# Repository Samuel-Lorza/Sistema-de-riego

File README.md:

# Sistema-de-riego automatico
Sistema de riego automatico con el uso del ESP32

## Integrantes:

Samuel Lorza-Miguel Pardo-Juan Crespo- Diego García

## Descripción

El presente proyecto, es un sistema de riego automático realizado con un microprocesador de referencia ESP32, la utilidad del sistema radica en la asistencia al usuario para regar plantas en momentos de ausencia, tales como un viaje, una reunión, o que el dueño este ocupado y no pueda cuidar de sus plantas. Con base en lo anterior, el sistema es totalmente programable en cuanto a la temperatura y la humedad que el usuario necesite, dependiendo de las necesidades de la planta. Se ha de mencionar que el usuario debe proveer de agua al sistema, por ejemplo, poniendo un tanque plástico con agua, además, el sistema hará un ruido con el objetivo de recordar al usuario de llenar el tanque (fuente de agua) cuando este tiene un bajo nivel de agua.

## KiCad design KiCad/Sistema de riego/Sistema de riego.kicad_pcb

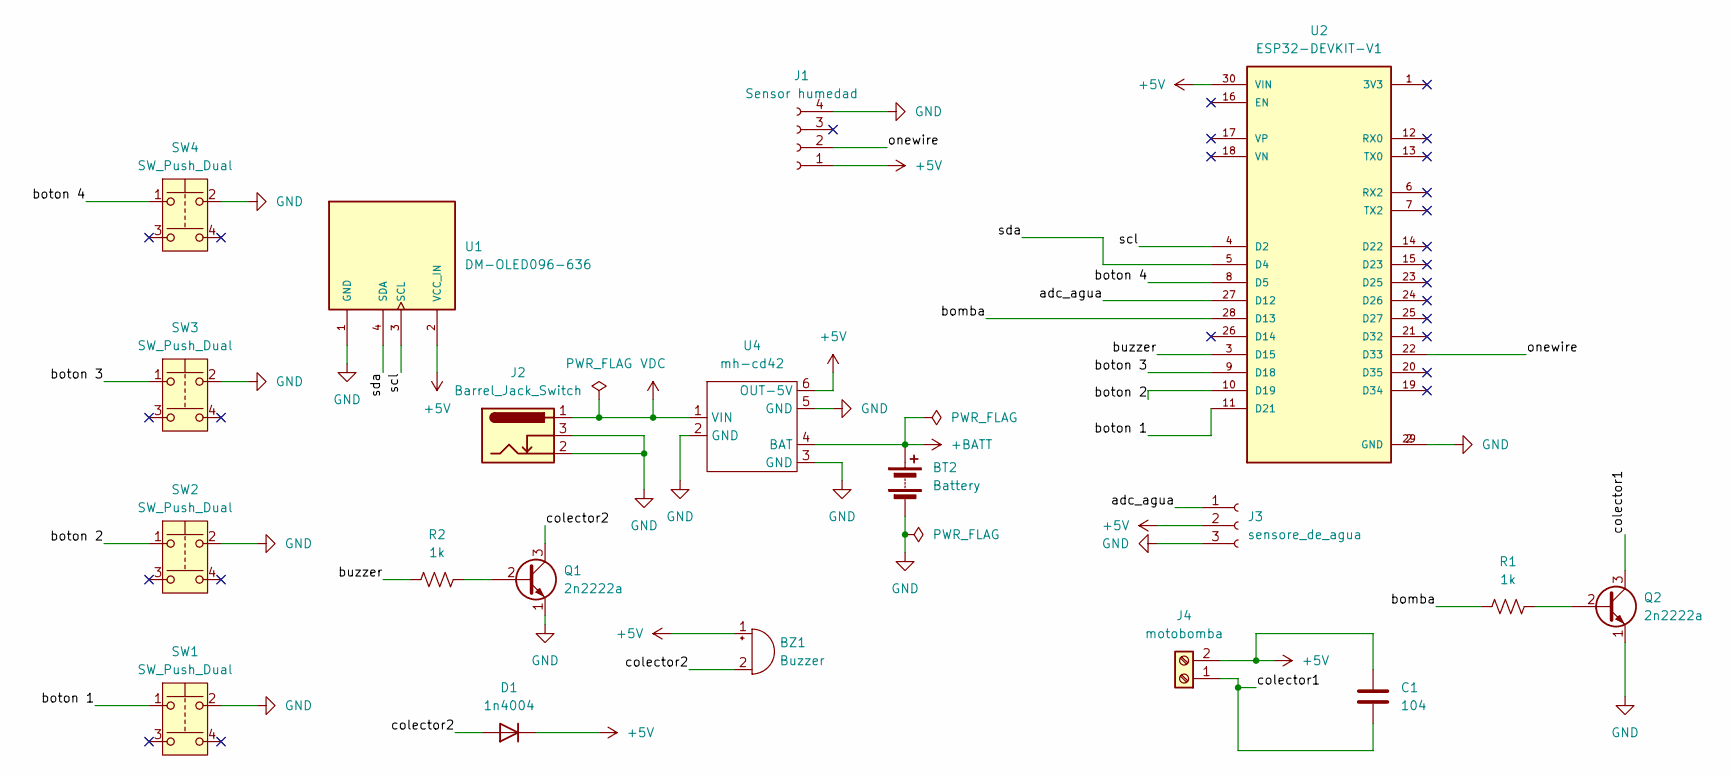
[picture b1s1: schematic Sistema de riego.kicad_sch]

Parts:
BT2: Battery; BatteryHolder_MPD_BH-18650-PC2
BZ1: Buzzer; Buzzer_15x7.5RM7.6
C1: 104; C_Disc_D6.0mm_W2.5mm_P5.00mm
D1: 1n4004; D_DO-15_P10.16mm_Horizontal
J1: Sensor humedad; PinSocket_1x04_P2.54mm_Vertical
J2: Barrel_Jack_Switch; BarrelJack_Horizontal
J3: sensore_de_agua; PinSocket_1x03_P2.54mm_Vertical
J4: motobomba; TerminalBlock_bornier-2_P5.08mm
Q1, Q2: 2n2222a; TO-92
R1, R2: 1k; R_Axial_DIN0207_L6.3mm_D2.5mm_P7.62mm_Horizontal
SW1, SW2, SW3, SW4: SW_Push_Dual; SW_PUSH_6mm_H4.3mm
U1: DM-OLED096-636; MODULE_DM-OLED096-636; PARTREV 2018-09-10
U2: ESP32-DEVKIT-V1; MODULE_ESP32_DEVKIT_V1; PARTREV N/A
U4: mh-cd42

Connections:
+5V: BZ1.1 (+), C1.1, D1.1 (K), J1.1, J3.2, J4.2, U1.2 (VCC_IN), U2.30 (VIN), U4.6 (OUT-5V)
+BATT: BT2.1 (+), U4.4 (BAT)
/adc_agua: J3.1, U2.27 (D12)
/bomba: R1.1, U2.28 (D13)
/boton 1: SW1.1, U2.11 (D21)
/boton 2: SW2.1, U2.10 (D19)
/boton 3: SW3.1, U2.9 (D18)
/boton 4: SW4.1, U2.8 (D5)
/buzzer: R2.1, U2.3 (D15)
/colector1: C1.2, J4.1, Q2.3 (C)
/colector2: BZ1.2 (-), D1.2 (A), Q1.3 (C)
/onewire: J1.2, U2.22 (D33)
/scl: U1.3 (SCL), U2.4 (D2)
/sda: U1.4 (SDA), U2.5 (D4)
GND: BT2.2 (-), J1.4, J2.2, J2.3, J3.3, Q1.1 (E), Q2.1 (E), SW1.2, SW2.2, SW3.2, SW4.2, U1.1 (GND), U2.2 (GND), U2.29 (GND), U4.2 (GND), U4.3 (GND), U4.5 (GND)
unnamed: Q1.2 (B), R2.2
unnamed: Q2.2 (B), R1.2
VDC: J2.1, U4.1 (VIN)

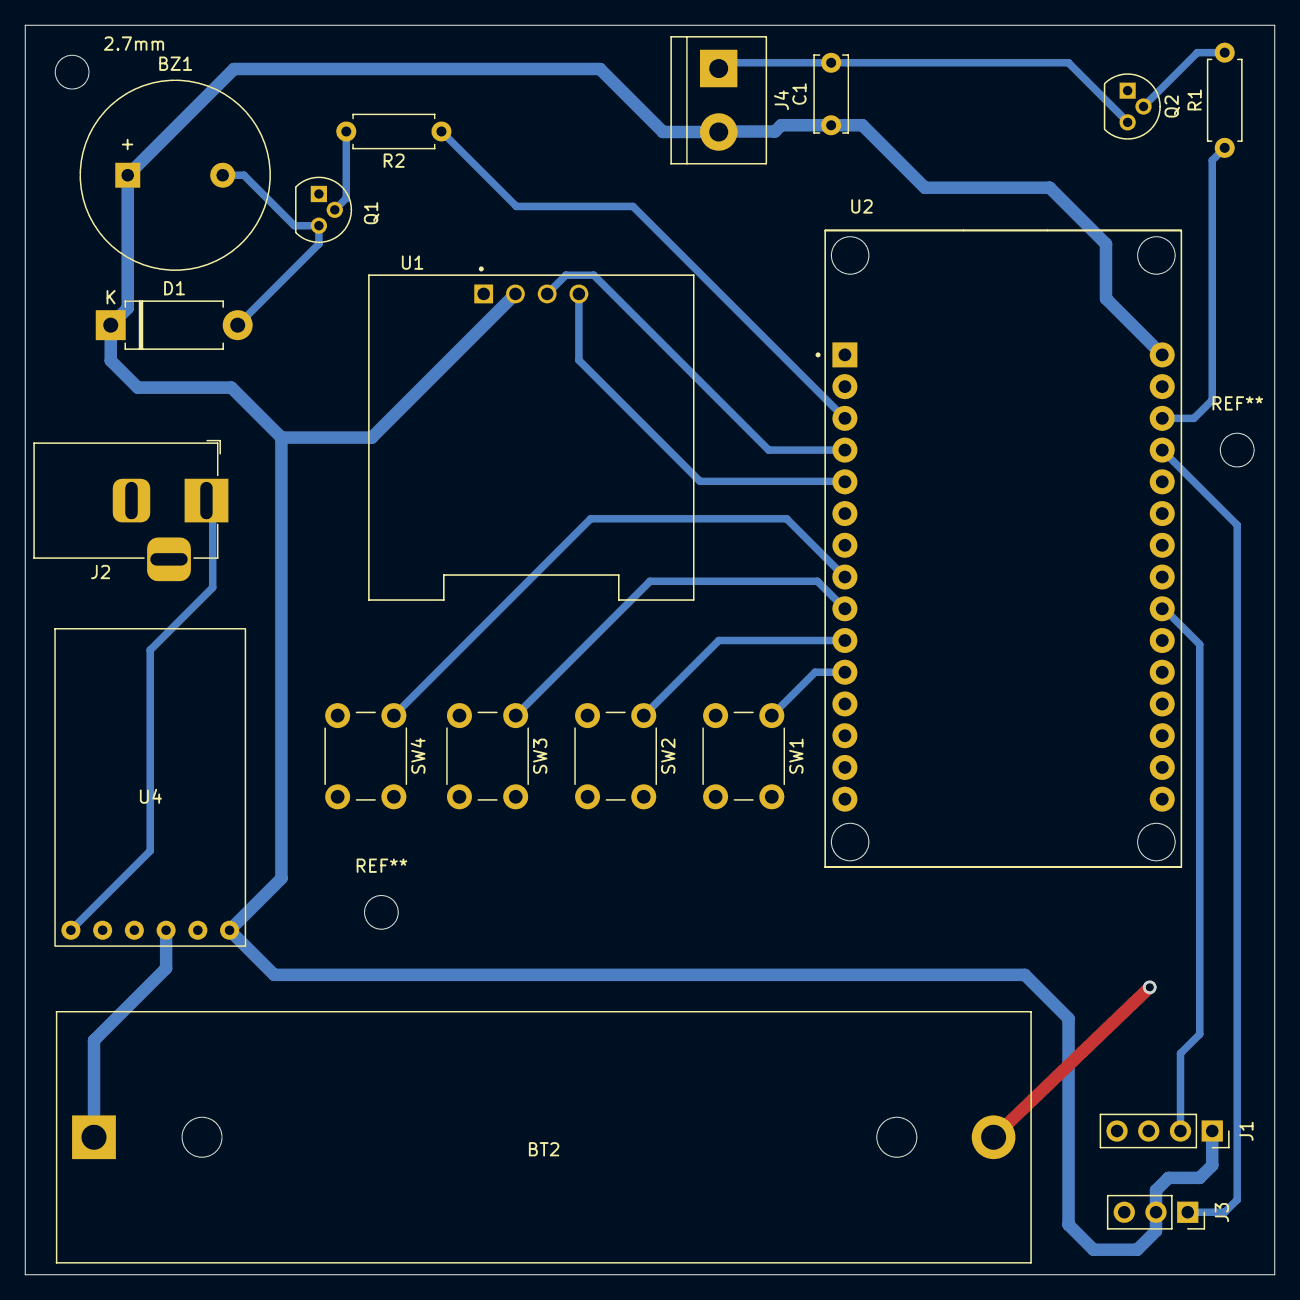
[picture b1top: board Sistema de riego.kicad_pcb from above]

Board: 2 copper layers, 100.0 x 100.0 mm, 20 parts (0 on the bottom side), 18 nets.

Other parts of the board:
2.7mm: MountingHole_2.7mm_M2.5

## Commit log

2024-08-29 Update README.md
    Añadir descripción
2024-08-31 Esquemático proyecto
2024-08-31 Esquemático PCB
    Añadir imagen del esquemático de la PCB del proyecto.
2024-08-31 Diagramas del funcionamiento del proyecto
2024-09-07 Esquematico PCB
2024-09-21 Actualización pruebas
2024-09-22 codigos de prueba y librerias
    Se subieron los códigos de prueba y librerías utilizadas
2024-09-23 Diseño de PCB KiCad
    Se subieron las imágenes de la PCB
2024-09-23 PCb pines soldados
2024-09-23 Sistema
2024-09-23 Imagen del poster
2024-09-23 Adicion de imagen
2024-09-23 Fotos Proyecto
2024-09-24 Error pantalla
2024-09-24 solución pantalla
2024-09-25 imagen
2024-09-25 subir codigo general
2024-09-25 KiCad
